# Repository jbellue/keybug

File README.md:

# Keybug - a small 5-keys macro keypad

It was initially designed to handle a debugger (Start/Stop/Step Into/Step Out/Step).

It runs [RMK](https://github.com/HaoboGu/rmk) (free vial!), but will be extremely simple to add to QMK. I might do that someday.

## Default Keymap

Here it is with the default keys to debug on IntelliJ:

```text
╭──────┬──────┬──────┬──────┬──────╮
│ Ctrl │  F9  │  F8  │  F7  │ Shft │
│  F2  │      │      │      │  F8  │
╰──────┴──────┴──────┴──────┴──────╯
```

## Remapping

Remapping is done through [Vial](https://vial.rocks/) on a browser supporting WedHID (i.e. Chrome).

Due to the way RMK works, reflashing probably doesn't update the keymap.

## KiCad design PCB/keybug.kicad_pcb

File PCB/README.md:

# Keybug's PCB

Built in Kicad8, using files from [Crides' Kleeb](https://github.com/crides/kleeb)

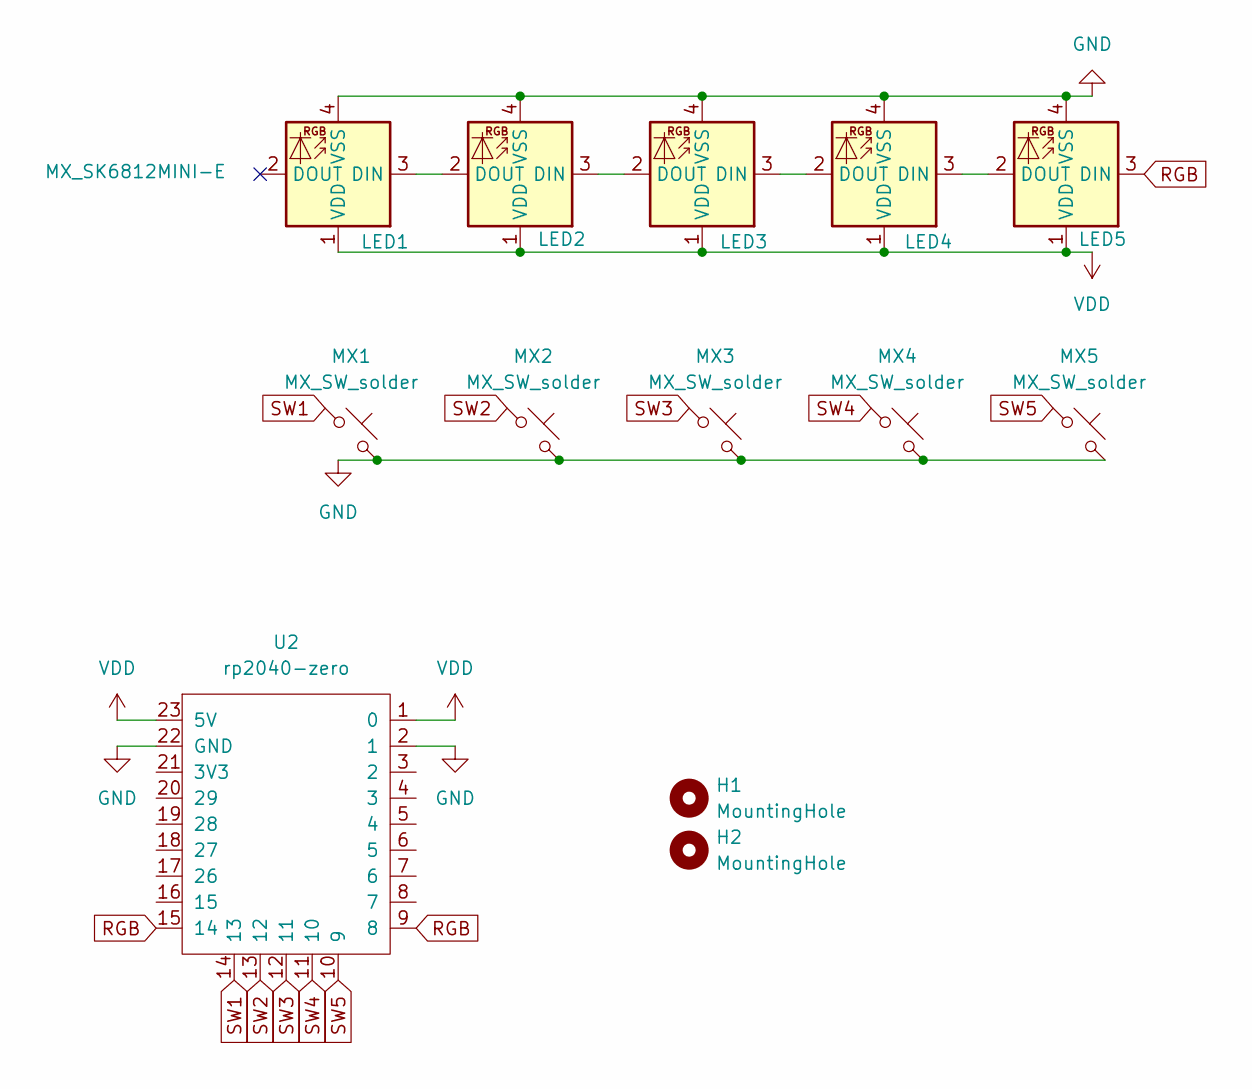
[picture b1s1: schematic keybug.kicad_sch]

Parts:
H1, H2: MountingHole; MountingHole_2.2mm_M2
LED1, LED2, LED3, LED4, LED5: MX_SK6812MINI-E; LED_MX_6028R-ROT
MX1, MX2, MX3, MX4, MX5: MX_SW_solder; SW_MX_1u
U2: rp2040-zero; rp2040-zero-tht

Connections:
GND: LED1.4 (VSS), LED2.4 (VSS), LED3.4 (VSS), LED4.4 (VSS), LED5.4 (VSS), MX1.2, MX2.2, MX3.2, MX4.2, MX5.2, U2.2 (1), U2.22 (GND)
unnamed: LED1.3 (DIN), LED2.2 (DOUT)
unnamed: LED2.3 (DIN), LED3.2 (DOUT)
unnamed: LED3.3 (DIN), LED4.2 (DOUT)
unnamed: LED4.3 (DIN), LED5.2 (DOUT)
RGB: LED5.3 (DIN), U2.9 (8), U2.15 (14)
SW1: MX1.1, U2.14 (13)
SW2: MX2.1, U2.13 (12)
SW3: MX3.1, U2.12 (11)
SW4: MX4.1, U2.11 (10)
SW5: MX5.1, U2.10 (9)
VDD: LED1.1 (VDD), LED2.1 (VDD), LED3.1 (VDD), LED4.1 (VDD), LED5.1 (VDD), U2.1 (0), U2.23 (5V)

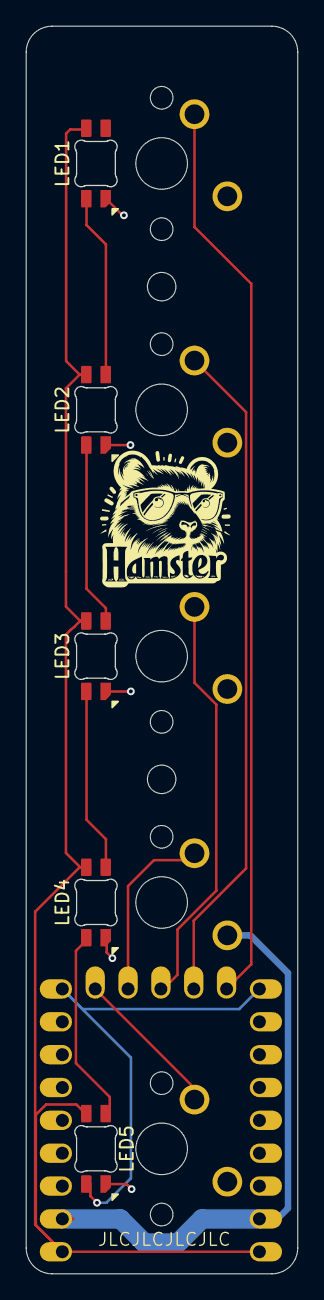
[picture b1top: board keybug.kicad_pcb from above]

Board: 2 copper layers, 21.0 x 96.4 mm, 13 parts (0 on the bottom side), 12 nets.

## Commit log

2024-11-12 Add firmware
2024-11-12 Add case
2024-11-12 Add PCB
2024-11-12 Add README and images
2024-11-12 Add main README
2024-11-18 bump rmk crate version
2024-11-18 set the firmware package data
2024-11-18 update keyboard.toml manufacturer
2024-11-18 Update default keymap
2024-11-19 Update keymap
2024-11-22 PCB - put switches pads on both sides...
2024-11-22 PCB - update Gerber.zip file
2024-11-22 Case - update case after first print
2024-11-25 case: add recess for pins
2024-11-29 firmware: bump rmk version
2024-12-11 Update pins to match the PCB issue...
2024-12-11 PCB+Firmware: make board reversible
2024-12-21 Add LEDs to PCB
